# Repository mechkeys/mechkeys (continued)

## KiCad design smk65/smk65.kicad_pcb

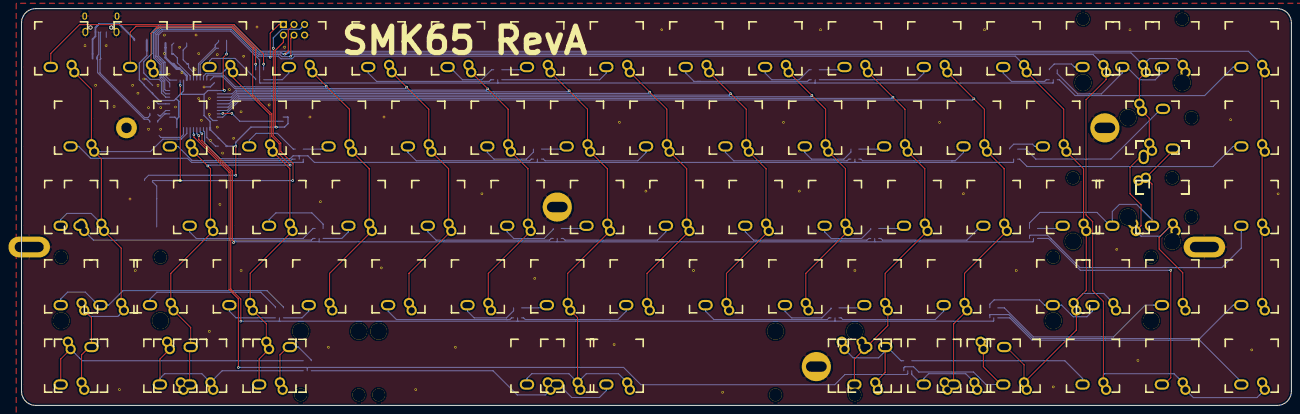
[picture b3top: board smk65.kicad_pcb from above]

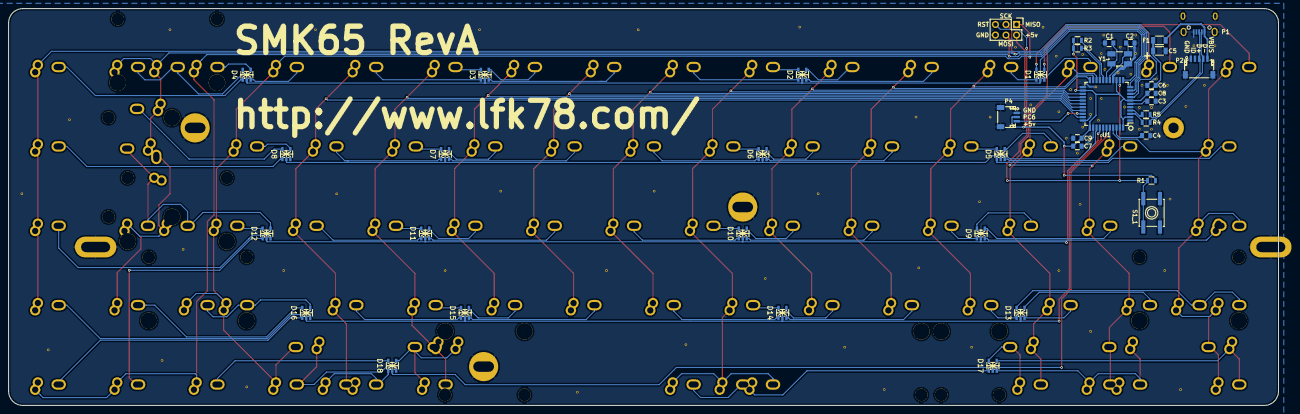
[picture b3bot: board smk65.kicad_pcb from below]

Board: 2 copper layers, 304.8 x 95.2 mm, 149 parts (40 on the bottom side), 107 nets.

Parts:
C1, C2: 18pF; C_0805
C3, C6, C7, C8, C9: 0.1µF; C_0805
C4: 1µF; C_0805
C5: 4.7µF; C_1206
D1, D2, D3, D4, D5, D6, D7, D8, D9, D10, D11, D12, D13, D14, D15, D16, D17, D18: 1SS309; SC-74A
F1: FP_Small; C_1206
MH1, MH2, MH3: MOUNT_HOLE; PKRH
MH4: MOUNT_HOLE; PKRHC
MH5, MH6: MOUNT_HOLE; PKRHSL
P1: USB_OTG; USB2_MICROB_WURTH
P2: CONN_01X05; JST_SH_SM05B-SRSS-TB_05x1.00mm_Angled
P3: CONN_02X03; Pin_Header_Straight_2x03
P4: CONN_01X03; JST_SH_SM03B-SRSS-TB_03x1.00mm_Angled
R1: 10k; R_0805
R2, R3: 4.7k; R_0805
R4, R5: 22; R_0805
S1, S2, S3, S4, S5, S6, S7, S8, S9, S10, S11, S12, S13, S14, S15, S16, S17, S18, S19, S20, S21, S22, S23, S24, S25, S26, S27, S28, S29, S30, S31, S32, S33, S34, S35, S36, S37, S38, S39, S40, S41, S42, S43, S44, S45, S46, S47, S48, S49, S50, S51, S52, S53, S54, S55, S56, S57, S58, S59, S60, S61, S62, S63, S64, S65, S66, S67, S68, S69, S70, S71, S115, S132, S145, S147, S159, S162, S163, S164, S165, S166, S167, S168, S245, S263, S265, S266, S345: MX_LED; SMK-Alps
S1_1: SW_PUSH; SW_SPST_EVQP0
STAB1, STAB2, STAB3, STAB4, STAB5, STAB6, STAB7, STAB8, STAB9, STAB10, STAB11, STAB12, STAB13, STAB14, STAB15: STAB
U1: ATmega32U4-AU; TQFP-44_10x10mm_Pitch0.8mm
Y1: CRYSTAL_SMD; Crystal_SMD_5032_4Pads

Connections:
+5v: C5.1, C6.1, C7.1, C8.1, C9.1, F1.2, P3.2, P4.2, R1.1, R2.1, R3.1, U1.2, U1.7, U1.14, U1.24, U1.34, U1.44
C1: S1.SW1, S17.SW1, S32.SW1, S47.SW1, S62.SW1, S132.SW2, S147.SW1, S162.SW2, U1.41
C2: S2.SW1, S18.SW1, S33.SW1, S48.SW1, S63.SW1, S163.SW2, S263.SW2, U1.40
C3: S3.SW1, S19.SW1, S34.SW1, S49.SW1, S64.SW2, S164.SW1, U1.20
C4: S4.SW1, S20.SW1, S35.SW1, S50.SW1, U1.21
C5: S5.SW1, S21.SW1, S36.SW1, S51.SW1, U1.22
C6: S6.SW1, S22.SW1, S37.SW1, S52.SW1, U1.25
C7: S7.SW1, S23.SW1, S38.SW1, S53.SW1, S65.SW1, S165.SW2, S265.SW1, U1.26
C8: S8.SW1, S24.SW1, S39.SW1, S54.SW1, U1.27
C9: S9.SW1, S25.SW1, S40.SW1, S55.SW1, U1.28
C10: S10.SW1, S26.SW1, S41.SW1, S56.SW1, U1.29
C11: S11.SW1, S27.SW1, S42.SW1, S57.SW1, S66.SW2, S166.SW2, S266.SW1, U1.30
C12: S12.SW1, S28.SW1, S43.SW1, S58.SW1, S67.SW1, S167.SW2, U1.32
C13: P3.1, S13.SW1, S29.SW1, S44.SW1, S59.SW1, S68.SW1, S159.SW1, S168.SW2, U1.11
C14: P3.4, S14.SW1, S69.SW1, S70.SW1, S71.SW1, U1.10
C15: P3.3, S15.SW1, S30.SW1, S45.SW1, S60.SW1, S115.SW1, S145.SW1, S245.SW2, S345.SW1, U1.9
C16: S16.SW1, S31.SW1, S46.SW1, S61.SW1, U1.8
D+: R5.1, U1.4
D-: R4.1, U1.3
GND: C1.1, C2.1, C3.2, C4.2, C5.2, C6.2, C7.2, C8.2, C9.2, MH1.1, MH2.1, MH3.1, MH4.1, MH5.1, MH6.1, P1.5, P2.1, P3.6, P4.1, S1_1.2, U1.5, U1.15, U1.23, U1.33, U1.35, U1.43, Y1.3
LED_SCL: R2.2, U1.18
LED_SDA: R3.2, U1.19
Matrix-S1-D1-5: D1.5, S1.SW2
Matrix-S2-D1-4: D1.4, S2.SW2
Matrix-S3-D1-3: D1.3, S3.SW2
Matrix-S4-D1-1: D1.1, S4.SW2
Matrix-S5-D2-3: D2.3, S5.SW2
Matrix-S6-D2-4: D2.4, S6.SW2
Matrix-S7-D2-5: D2.5, S7.SW2
Matrix-S8-D2-1: D2.1, S8.SW2
Matrix-S9-D3-3: D3.3, S9.SW2
Matrix-S10-D3-4: D3.4, S10.SW2
Matrix-S11-D3-5: D3.5, S11.SW2
Matrix-S12-D3-1: D3.1, S12.SW2
Matrix-S13-D4-3: D4.3, S13.SW2
Matrix-S14-D4-4: D4.4, S14.SW2
Matrix-S15-D4-5: D4.5, S15.SW2, S115.SW2
Matrix-S16-D4-1: D4.1, S16.SW2
Matrix-S17-D5-1: D5.1, S17.SW2
Matrix-S18-D5-3: D5.3, S18.SW2
Matrix-S19-D5-4: D5.4, S19.SW2
Matrix-S20-D5-5: D5.5, S20.SW2
Matrix-S21-D6-3: D6.3, S21.SW2
Matrix-S22-D6-4: D6.4, S22.SW2
Matrix-S23-D6-5: D6.5, S23.SW2
Matrix-S24-D6-1: D6.1, S24.SW2
Matrix-S25-D7-3: D7.3, S25.SW2
Matrix-S26-D7-4: D7.4, S26.SW2
Matrix-S27-D7-5: D7.5, S27.SW2
Matrix-S28-D7-1: D7.1, S28.SW2
Matrix-S29-D8-4: D8.4, S29.SW2
Matrix-S30-D8-5: D8.5, S30.SW2
Matrix-S31-D8-1: D8.1, S31.SW2
Matrix-S32-D9-3: D9.3, S32.SW2, S132.SW1
Matrix-S33-D9-4: D9.4, S33.SW2
Matrix-S34-D9-5: D9.5, S34.SW2
Matrix-S35-D9-1: D9.1, S35.SW2
Matrix-S36-D10-3: D10.3, S36.SW2
Matrix-S37-D10-4: D10.4, S37.SW2
Matrix-S38-D10-5: D10.5, S38.SW2
Matrix-S39-D10-1: D10.1, S39.SW2
Matrix-S40-D11-3: D11.3, S40.SW2
Matrix-S41-D11-4: D11.4, S41.SW2
Matrix-S42-D11-5: D11.5, S42.SW2
Matrix-S43-D11-1: D11.1, S43.SW2
Matrix-S44-D12-5: D12.5, S44.SW2
Matrix-S45-D12-4: D12.4, S45.SW2, S145.SW2, S245.SW1, S345.SW2
Matrix-S46-D12-3: D12.3, S46.SW2
Matrix-S47-D13-5: D13.5, S47.SW2, S147.SW2
Matrix-S48-D13-4: D13.4, S48.SW2
Matrix-S49-D13-3: D13.3, S49.SW2
Matrix-S50-D13-1: D13.1, S50.SW2
Matrix-S51-D14-3: D14.3, S51.SW2
Matrix-S52-D14-4: D14.4, S52.SW2
Matrix-S53-D14-5: D14.5, S53.SW2
Matrix-S54-D14-1: D14.1, S54.SW2
Matrix-S55-D15-3: D15.3, S55.SW2
Matrix-S56-D15-4: D15.4, S56.SW2
Matrix-S57-D15-5: D15.5, S57.SW2
Matrix-S58-D15-1: D15.1, S58.SW2
Matrix-S59-D16-4: D16.4, S59.SW2, S159.SW2
Matrix-S60-D16-5: D16.5, S60.SW2
Matrix-S61-D16-3: D16.3, S61.SW2
Matrix-S62-D17-4: D17.4, S62.SW2, S162.SW1
Matrix-S63-D17-3: D17.3, S63.SW2, S163.SW1, S263.SW1
Matrix-S64-D17-5: D17.5, S64.SW1, S164.SW2
Matrix-S65-D17-1: D17.1, S65.SW2, S165.SW1, S265.SW2
Matrix-S66-D18-4: D18.4, S66.SW1, S166.SW1, S266.SW2
Matrix-S67-D18-1: D18.1, S67.SW2, S167.SW1
Matrix-S68-D18-3: D18.3, S68.SW2, S168.SW1
Matrix-S69-D18-5: D18.5, S69.SW2
Matrix-S70-D12-1: D12.1, S70.SW2
Matrix-S71-D16-1: D16.1, S71.SW2
unnamed: C1.2, U1.17, Y1.1
unnamed: C2.2, U1.16, Y1.2
unnamed: C3.1, U1.6
unnamed: C4.1, U1.42
unnamed: P4.3, U1.31
R1: D1.2, D2.2, D3.2, D4.2, U1.12
R2: D5.2, D6.2, D7.2, D8.2, U1.36
R3: D9.2, D10.2, D11.2, D12.2, U1.37
R4: D13.2, D14.2, D15.2, D16.2, U1.38
R5: D17.2, D18.2, U1.39
RESET: P3.5, R1.2, S1_1.1, U1.13
USB+: P1.3, P2.3, R5.2
USB-: P1.2, P2.4, R4.2
VBUS: F1.1, P1.1, P2.5

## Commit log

2017-07-20 Adding the SMK65, an SMK/Alps compatible PCB based on the WhiteFox
2017-08-11 Added svg of switches for smk65
